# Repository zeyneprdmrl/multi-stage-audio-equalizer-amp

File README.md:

# multi-stage-audio-equalizer-amp
Multi-stage analog audio equalizer and power amplifier (2N2222A BJT buffer, tunable 40 Hz–19.6 kHz RC band-pass filter, 2N7000 MOSFET gain stage, LM386 power amp) with 2-layer KiCad PCB.

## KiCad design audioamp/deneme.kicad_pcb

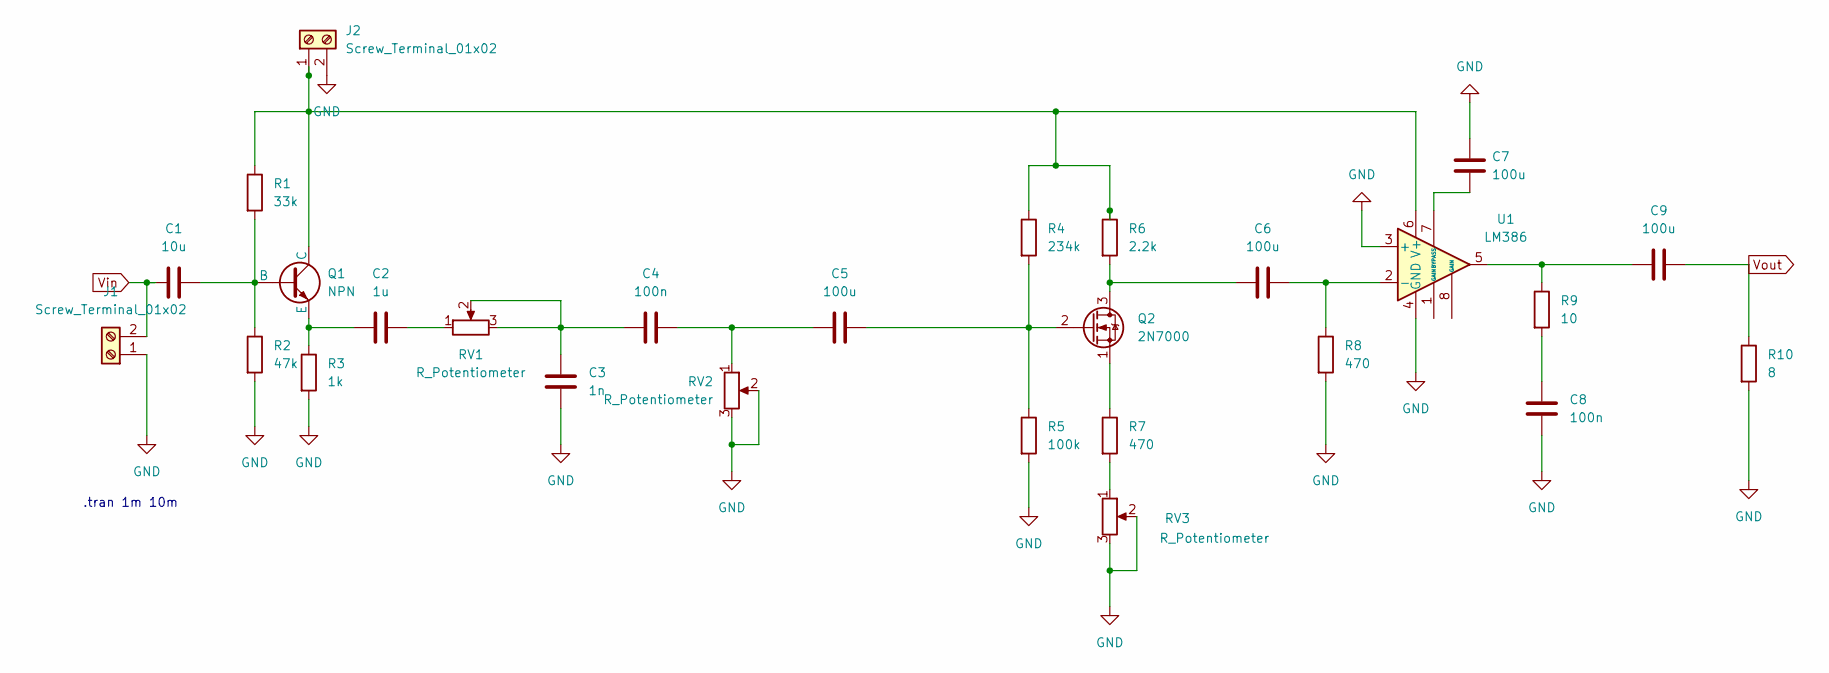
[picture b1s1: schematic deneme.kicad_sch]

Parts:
C1: 10u; C_Disc_D5.0mm_W2.5mm_P2.50mm
C2: 1u; C_Disc_D5.0mm_W2.5mm_P2.50mm
C3: 1n; C_Disc_D5.0mm_W2.5mm_P5.00mm
C4, C8: 100n; C_Disc_D5.0mm_W2.5mm_P5.00mm
C5, C6, C7, C9: 100u; CP_Radial_D6.3mm_P2.50mm
J1, J2: Screw_Terminal_01x02; TerminalBlock_Phoenix_PT-1,5-2-5.0-H_1x02_P5.00mm_Horizontal
Q1: NPN; TO-92_Inline
Q2: 2N7000; TO-92_Inline
R1: 33k; R_Axial_DIN0207_L6.3mm_D2.5mm_P7.62mm_Horizontal
R2: 47k; R_Axial_DIN0207_L6.3mm_D2.5mm_P7.62mm_Horizontal
R3: 1k; R_Axial_DIN0207_L6.3mm_D2.5mm_P7.62mm_Horizontal
R4: 234k; R_Axial_DIN0207_L6.3mm_D2.5mm_P7.62mm_Horizontal
R5: 100k; R_Axial_DIN0207_L6.3mm_D2.5mm_P7.62mm_Horizontal
R6: 2.2k; R_Axial_DIN0207_L6.3mm_D2.5mm_P7.62mm_Horizontal
R7, R8: 470; R_Axial_DIN0207_L6.3mm_D2.5mm_P7.62mm_Horizontal
R9: 10; R_Axial_DIN0207_L6.3mm_D2.5mm_P7.62mm_Horizontal
R10: 8; R_Axial_DIN0207_L6.3mm_D2.5mm_P7.62mm_Horizontal
RV1, RV2, RV3: R_Potentiometer; Potentiometer_Bourns_PTV09A-1_Single_Vertical
U1: LM386; CERDIP-8_W7.62mm_SideBrazed

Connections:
GND: C3.2, C7.2, C8.2, J1.1, J2.2, R2.2, R3.2, R5.2, R8.2, R10.2, RV2.2, RV2.3, RV3.2, RV3.3, U1.3 (+), U1.4 (GND)
unnamed: C2.2, RV1.1
unnamed: C3.1, C4.1, RV1.2, RV1.3
unnamed: C4.2, C5.1, RV2.1
unnamed: C8.1, R9.2
unnamed: C9.1, R9.1, U1.5
unnamed: J2.1, Q1.1 (C), R1.1, R4.1, R6.1, U1.6 (V+)
unnamed: C1.2, Q1.2 (B), R1.2, R2.1
unnamed: C2.1, Q1.3 (E), R3.1
unnamed: C6.1, Q2.3 (D), R6.2
unnamed: C5.2, Q2.2 (G), R4.2, R5.1
unnamed: Q2.1 (S), R7.1
unnamed: R7.2, RV3.1
unnamed: C6.2, R8.1, U1.2 (-)
unnamed: C7.1, U1.7 (BYPASS)
Vin: C1.1, J1.2
Vout: C9.2, R10.1

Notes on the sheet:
.tran 1m 10m

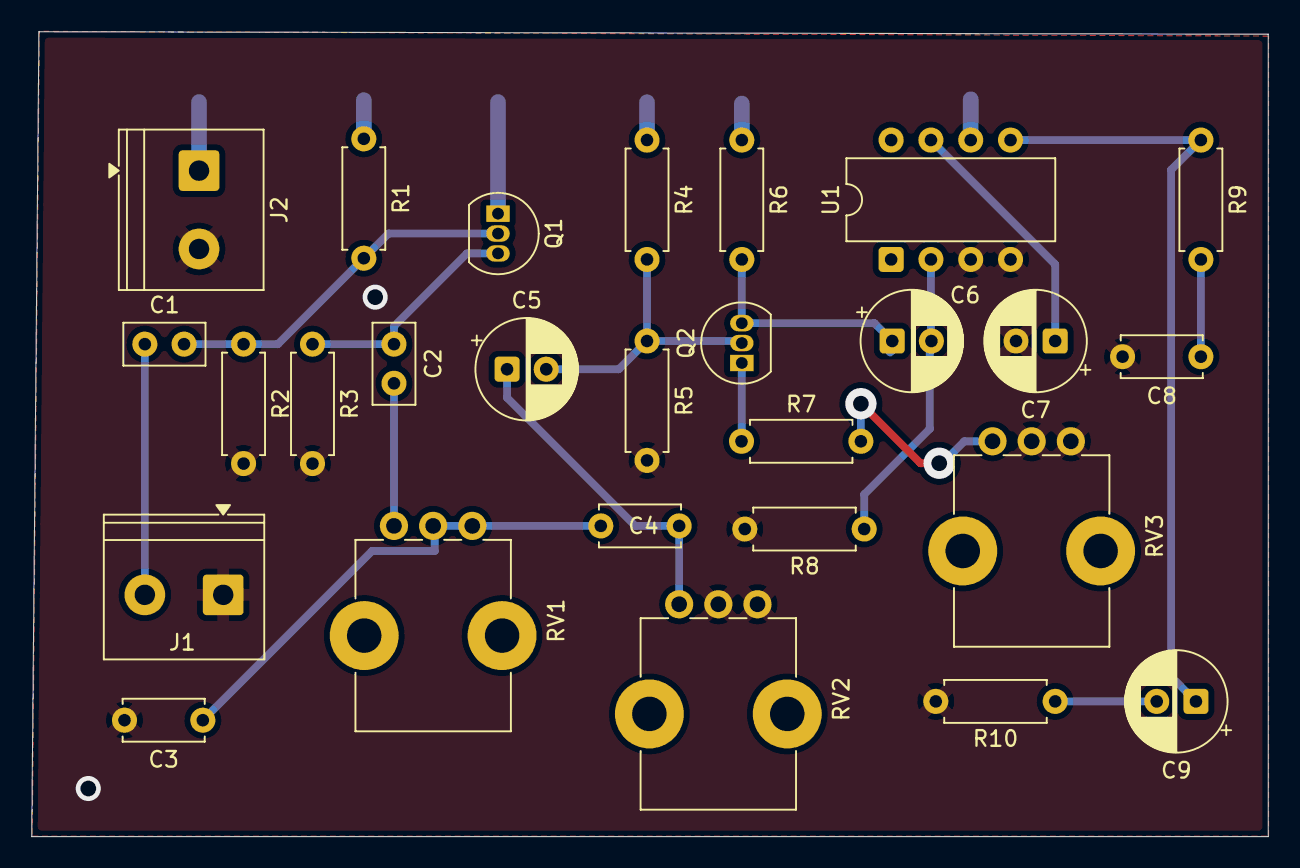
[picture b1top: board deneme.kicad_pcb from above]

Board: 2 copper layers, 78.9 x 51.4 mm, 27 parts (0 on the bottom side), 17 nets.
